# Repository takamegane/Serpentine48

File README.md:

# Serpentine48
 
## 必要なパーツ
* RP2040 zero x2  
* 1N4148W SMDダイオード x48  
* TRRS ジャック x2
* kailh スイッチソケット(MX用) x42-48
* kailh スイッチソケット(choc用) x42-48
* cherry MX互換キースイッチor choc互換スイッチ x42-48  
* EC12互換ロータリーエンコーダ x0-6    
* キーキャップ   
* USB Type-cケーブル x1  
* 丸スペーサー M2x7mm x10
* 丸スペーサー M2X8mm以上 x6
* ネジ M2x4mm x32

## はんだ付けについて
一般的な自作キーボードと作業は同じです。ダイオードの向きには注意してください。  
RP2040 zeroはコンスルーもしくはピンヘッダでの取り付けとなります。向きに注意してください。
ブートスイッチ等が上にくる形ではんだ付けをしてください。

## ファームウェアについて
vialでキーマップを変更できます。基本的なファームとなっているため、好みに合わせてキーマップを作成しなおしてください。

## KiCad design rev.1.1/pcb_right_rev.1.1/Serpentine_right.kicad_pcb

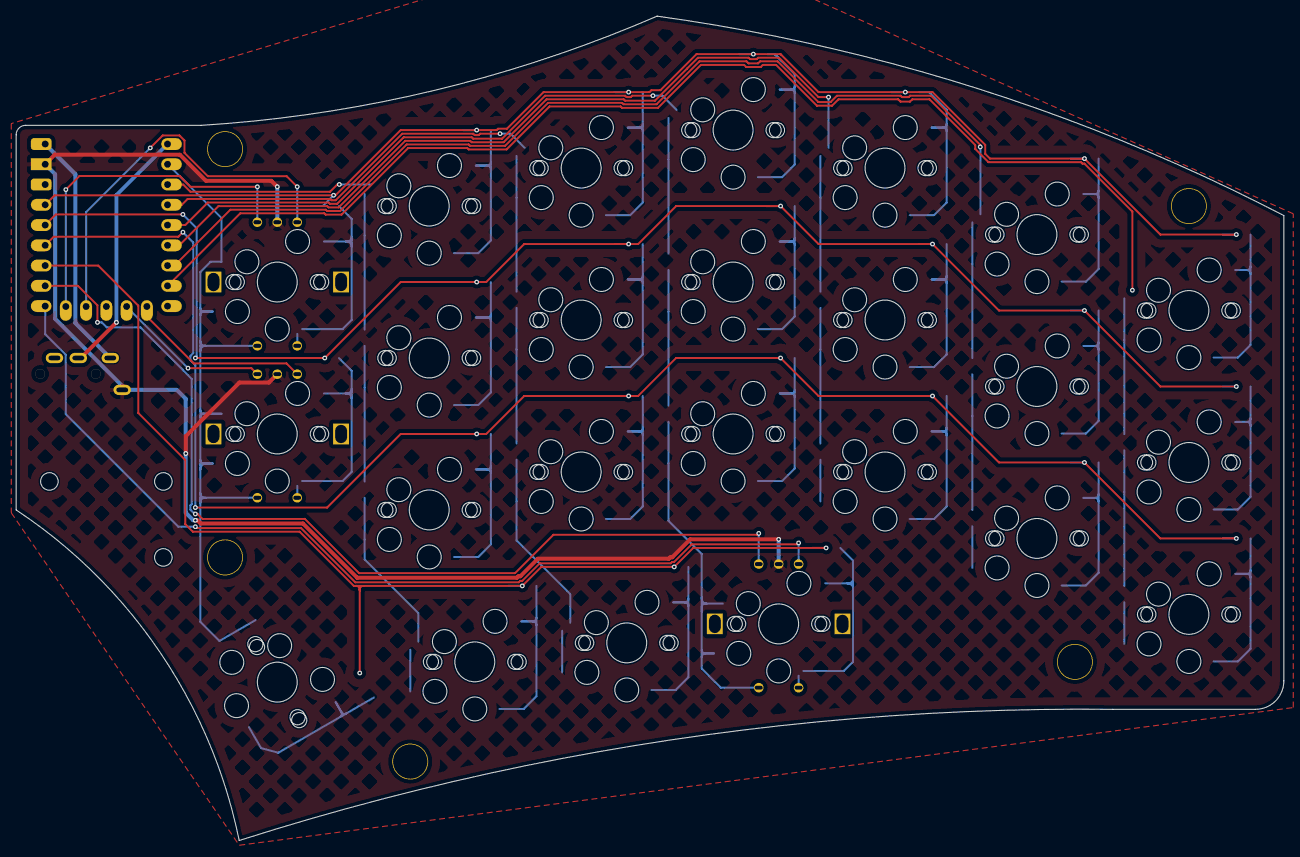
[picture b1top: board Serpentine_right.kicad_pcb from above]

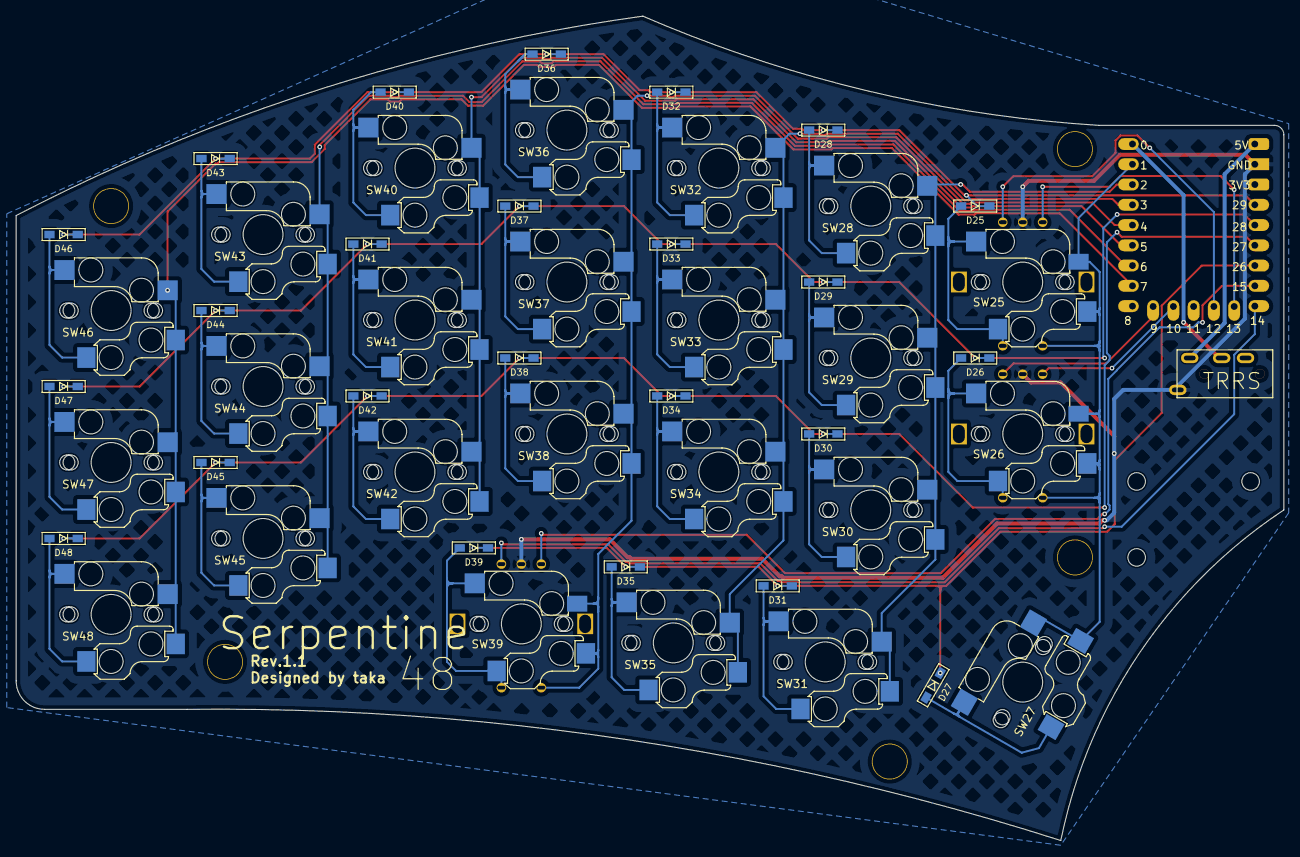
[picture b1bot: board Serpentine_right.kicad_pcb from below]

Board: 2 copper layers, 158.9 x 103.4 mm, 58 parts (2 on the bottom side), 44 nets.

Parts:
D25, D26, D27, D28, D29, D30, D31, D32, D33, D34, D35, D36, D37, D38, D39, D40, D41, D42, D43, D44, D45, D46, D47, D48: D; Diode_SMD
JACK2: MJ-4PP-9; TRRS_MJ-4PP-9_1
Ref**: Val**; m2_Spacer_Hole
Ref**#2, Ref**#4, Ref**#6: Val**; m2_Screw_Hole
Ref**#3, Ref**#5, Ref**#7, Ref**#8: Val**; m2_Spacer_Hole
SW25, SW26, SW39: RotaryEncoder_Switch; Kailh FullPOM MX_Hotswap_RE
SW27, SW28, SW29, SW30, SW31, SW32, SW33, SW34, SW35, SW36, SW37, SW38, SW40, SW41, SW42, SW43, SW44, SW45, SW46, SW47, SW48: SW_Push; Kailh FullPOM MX_Hotswap
U2: RP2040-Zero; RP2040 Zero

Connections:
+5VR: JACK2.D, U2.32 (5V)
Col7: SW25.S2, SW26.S2, SW27.1, U2.1
Col8: SW28.1, SW29.1, SW30.1, SW31.1, U2.2
Col9: SW32.1, SW33.1, SW34.1, SW35.1, U2.3
Col10: SW36.1, SW37.1, SW38.1, SW39.S2, U2.4
Col11: SW40.1, SW41.1, SW42.1, U2.5
Col12: SW43.1, SW44.1, SW45.1, U2.6
Col13: SW46.1, SW47.1, SW48.1, U2.7
DATA_R: JACK2.C, U2.0
GNDR: JACK2.A, SW25.C, SW26.C, SW39.C, U2.31 (GND)
unnamed: D25.2 (A), SW25.S1
unnamed: D26.2 (A), SW26.S1
unnamed: D27.2 (A), SW27.2
unnamed: D28.2 (A), SW28.2
unnamed: D29.2 (A), SW29.2
unnamed: D30.2 (A), SW30.2
unnamed: D31.2 (A), SW31.2
unnamed: D32.2 (A), SW32.2
unnamed: D33.2 (A), SW33.2
unnamed: D34.2 (A), SW34.2
unnamed: D35.2 (A), SW35.2
unnamed: D36.2 (A), SW36.2
unnamed: D37.2 (A), SW37.2
unnamed: D38.2 (A), SW38.2
unnamed: D39.2 (A), SW39.S1
unnamed: D40.2 (A), SW40.2
unnamed: D41.2 (A), SW41.2
unnamed: D42.2 (A), SW42.2
unnamed: D43.2 (A), SW43.2
unnamed: D44.2 (A), SW44.2
unnamed: D45.2 (A), SW45.2
unnamed: D46.2 (A), SW46.2
unnamed: D47.2 (A), SW47.2
unnamed: D48.2 (A), SW48.2
RE4A: SW39.A, U2.14
RE4B: SW39.B, U2.15
RE5A: SW25.A, U2.12
RE5B: SW25.B, U2.13
RE6A: SW26.A, U2.9
RE6B: SW26.B, U2.10
Row4: D25.1 (K), D28.1 (K), D32.1 (K), D36.1 (K), D40.1 (K), D43.1 (K), D46.1 (K), U2.29
Row5: D26.1 (K), D29.1 (K), D33.1 (K), D37.1 (K), D41.1 (K), D44.1 (K), D47.1 (K), U2.28
Row6: D30.1 (K), D34.1 (K), D38.1 (K), D42.1 (K), D45.1 (K), D48.1 (K), U2.27
Row7: D27.1 (K), D31.1 (K), D35.1 (K), D39.1 (K), U2.26

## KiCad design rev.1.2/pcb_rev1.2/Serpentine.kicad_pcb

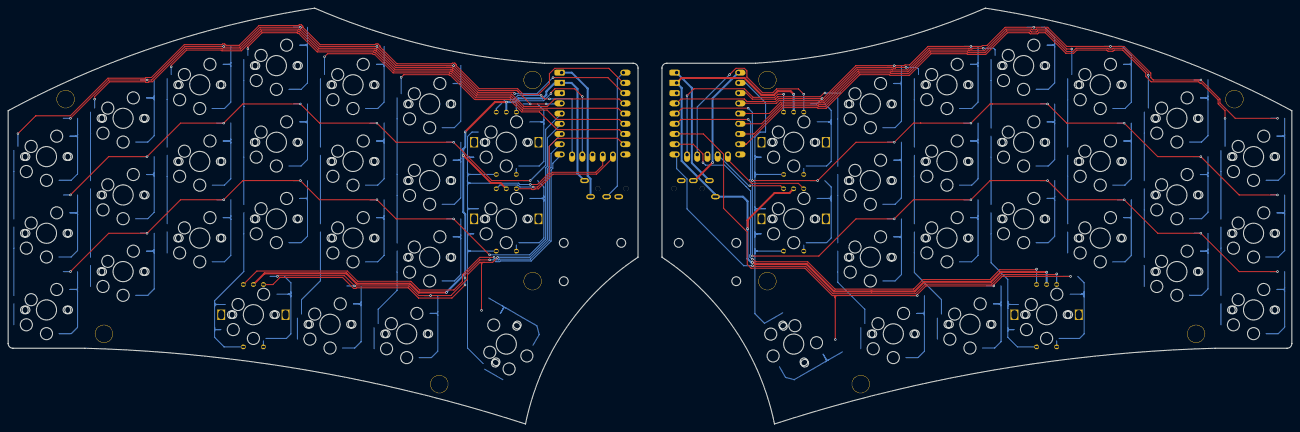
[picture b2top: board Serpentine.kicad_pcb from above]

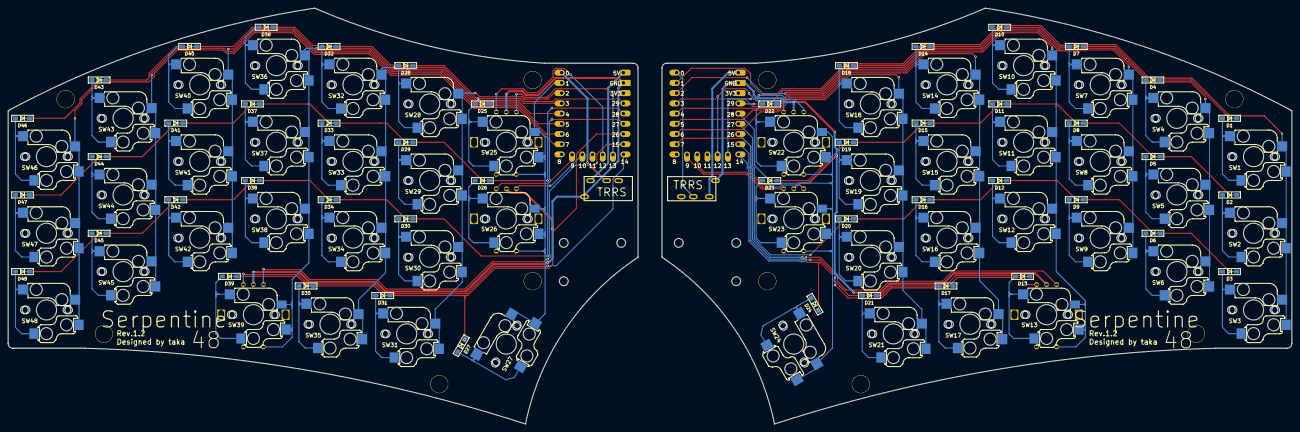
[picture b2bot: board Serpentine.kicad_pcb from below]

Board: 2 copper layers, 319.1 x 103.4 mm, 116 parts (3 on the bottom side), 88 nets.

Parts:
D1, D2, D3, D4, D5, D6, D7, D8, D9, D10, D11, D12, D13, D14, D15, D16, D17, D18, D19, D20, D21, D22, D23, D24, D25, D26, D27, D28, D29, D30, D31, D32, D33, D34, D35, D36, D37, D38, D39, D40, D41, D42, D43, D44, D45, D46, D47, D48: D; Diode_SMD
JACK1, JACK2: MJ-4PP-9; TRRS_MJ-4PP-9_1
Ref**: Val**; m2_Screw_Hole
Ref**#2, Ref**#3, Ref**#6, Ref**#11, Ref**#12: Val**; m2_Screw_Hole
Ref**#4, Ref**#5, Ref**#7, Ref**#8, Ref**#9, Ref**#10, Ref**#13, Ref**#14, Ref**#15, Ref**#16: Val**; m2_Spacer_Hole
SW1, SW2, SW3, SW4, SW5, SW6, SW7, SW8, SW9, SW10, SW11, SW12, SW14, SW15, SW16, SW17, SW18, SW19, SW20, SW21, SW24, SW27, SW28, SW29, SW30, SW31, SW32, SW33, SW34, SW35, SW36, SW37, SW38, SW40, SW41, SW42, SW43, SW44, SW45, SW46, SW47, SW48: SW_Push; Kailh FullPOM MX_Hotswap
SW13, SW22, SW23, SW25, SW26, SW39: RotaryEncoder_Switch; Kailh FullPOM MX_Hotswap_RE
U1, U2: RP2040-Zero; RP2040 Zero

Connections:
+5V: JACK1.D, U1.32 (5V)
+5VR: JACK2.D, U2.32 (5V)
Col0: SW1.1, SW2.1, SW3.1, U1.1
Col1: SW4.1, SW5.1, SW6.1, U1.2
Col2: SW7.1, SW8.1, SW9.1, U1.3
Col3: SW10.1, SW11.1, SW12.1, SW13.S2, U1.4
Col4: SW14.1, SW15.1, SW16.1, SW17.1, U1.5
Col5: SW18.1, SW19.1, SW20.1, SW21.1, U1.6
Col6: SW22.S2, SW23.S2, SW24.1, U1.7
Col7: SW25.S2, SW26.S2, SW27.1, U2.1
Col8: SW28.1, SW29.1, SW30.1, SW31.1, U2.2
Col9: SW32.1, SW33.1, SW34.1, SW35.1, U2.3
Col10: SW36.1, SW37.1, SW38.1, SW39.S2, U2.4
Col11: SW40.1, SW41.1, SW42.1, U2.5
Col12: SW43.1, SW44.1, SW45.1, U2.6
Col13: SW46.1, SW47.1, SW48.1, U2.7
DATA_L: JACK1.C, U1.0
DATA_R: JACK2.C, U2.0
GND: JACK1.A, SW13.C, SW22.C, SW23.C, U1.31 (GND)
GNDR: JACK2.A, SW25.C, SW26.C, SW39.C, U2.31 (GND)
unnamed: D1.2 (A), SW1.2
unnamed: D2.2 (A), SW2.2
unnamed: D3.2 (A), SW3.2
unnamed: D4.2 (A), SW4.2
unnamed: D5.2 (A), SW5.2
unnamed: D6.2 (A), SW6.2
unnamed: D7.2 (A), SW7.2
unnamed: D8.2 (A), SW8.2
unnamed: D9.2 (A), SW9.2
unnamed: D10.2 (A), SW10.2
unnamed: D11.2 (A), SW11.2
unnamed: D12.2 (A), SW12.2
unnamed: D13.2 (A), SW13.S1
unnamed: D14.2 (A), SW14.2
unnamed: D15.2 (A), SW15.2
unnamed: D16.2 (A), SW16.2
unnamed: D17.2 (A), SW17.2
unnamed: D18.2 (A), SW18.2
unnamed: D19.2 (A), SW19.2
unnamed: D20.2 (A), SW20.2
unnamed: D21.2 (A), SW21.2
unnamed: D22.2 (A), SW22.S1
unnamed: D23.2 (A), SW23.S1
unnamed: D24.2 (A), SW24.2
unnamed: D25.2 (A), SW25.S1
unnamed: D26.2 (A), SW26.S1
unnamed: D27.2 (A), SW27.2
unnamed: D28.2 (A), SW28.2
unnamed: D29.2 (A), SW29.2
unnamed: D30.2 (A), SW30.2
unnamed: D31.2 (A), SW31.2
unnamed: D32.2 (A), SW32.2
unnamed: D33.2 (A), SW33.2
unnamed: D34.2 (A), SW34.2
unnamed: D35.2 (A), SW35.2
unnamed: D36.2 (A), SW36.2
unnamed: D37.2 (A), SW37.2
unnamed: D38.2 (A), SW38.2
unnamed: D39.2 (A), SW39.S1
unnamed: D40.2 (A), SW40.2
unnamed: D41.2 (A), SW41.2
unnamed: D42.2 (A), SW42.2
unnamed: D43.2 (A), SW43.2
unnamed: D44.2 (A), SW44.2
unnamed: D45.2 (A), SW45.2
unnamed: D46.2 (A), SW46.2
unnamed: D47.2 (A), SW47.2
unnamed: D48.2 (A), SW48.2
RE1A: SW13.A, U1.14
RE1B: SW13.B, U1.15
RE2A: SW22.A, U1.12
RE2B: SW22.B, U1.13
RE3A: SW23.A, U1.9
RE3B: SW23.B, U1.10
RE4A: SW39.A, U2.14
RE4B: SW39.B, U2.15
RE5A: SW25.A, U2.12
RE5B: SW25.B, U2.13
RE6A: SW26.A, U2.9
RE6B: SW26.B, U2.10
Row0: D1.1 (K), D4.1 (K), D7.1 (K), D10.1 (K), D14.1 (K), D18.1 (K), D22.1 (K), U1.29
Row1: D2.1 (K), D5.1 (K), D8.1 (K), D11.1 (K), D15.1 (K), D19.1 (K), D23.1 (K), U1.28
Row2: D3.1 (K), D6.1 (K), D9.1 (K), D12.1 (K), D16.1 (K), D20.1 (K), U1.27
Row3: D13.1 (K), D17.1 (K), D21.1 (K), D24.1 (K), U1.26
Row4: D25.1 (K), D28.1 (K), D32.1 (K), D36.1 (K), D40.1 (K), D43.1 (K), D46.1 (K), U2.29
Row5: D26.1 (K), D29.1 (K), D33.1 (K), D37.1 (K), D41.1 (K), D44.1 (K), D47.1 (K), U2.28
Row6: D30.1 (K), D34.1 (K), D38.1 (K), D42.1 (K), D45.1 (K), D48.1 (K), U2.27
Row7: D27.1 (K), D31.1 (K), D35.1 (K), D39.1 (K), U2.26

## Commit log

2025-03-20 file delete
2025-05-01 add file
2025-05-09 add firmware
2025-05-24 add 20layer
